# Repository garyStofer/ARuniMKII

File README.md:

# ARuniMKII
PCB  to run ERSKY firmware on old RC transmitters or DIY boxes.

-- Originated from AR9X and ARUni schematic as designed by "flygear" -- on RCgroups

See thread AR9X and ARUni on RC-Groups

Firmware discussions at openrcforums.com under erskyTx (was ersky9x)

Firmware can be found at er9x.com  maintained by Mike Blandford. Use ERSKYTX version  "9XR-PRO" 
Also Pre-Release FW at OpenRCforums : ErskyTX Test Versions by Mike Blandford.

The board is built with an AT-SAM-4 chip with twice the RAM of the original ARUni/AR9x board. See BOM file .
 
The correct chip ID has to be chosen when initially flashing the FW and bootloader to a blank chip with the SAMba tool from Atmel.

firmware src for jr9303 based implementation is at github.com/garyStofer/mbtx

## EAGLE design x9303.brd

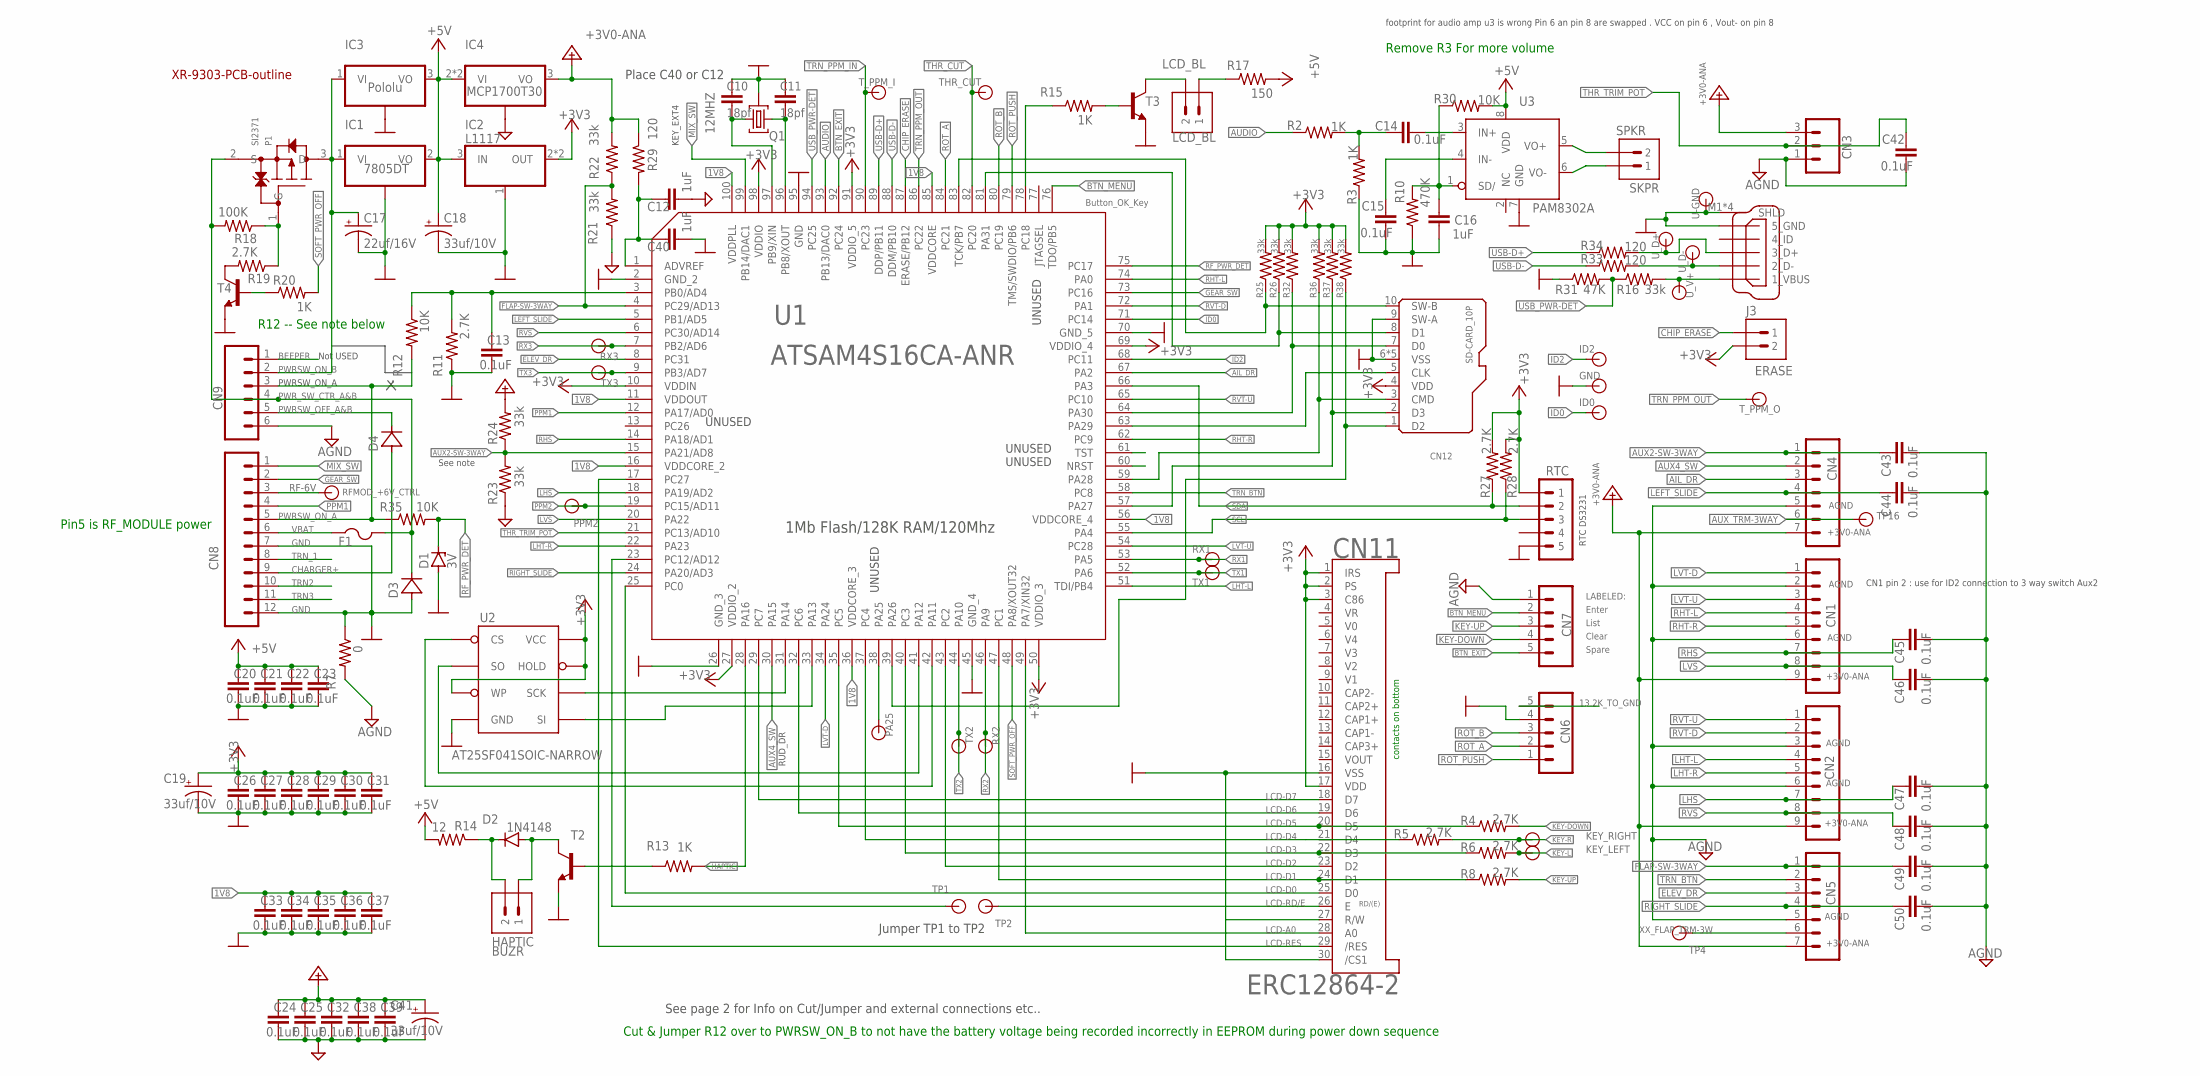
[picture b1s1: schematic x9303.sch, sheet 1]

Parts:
BUZR: HAPTIC; 1X02
C10, C11: 18pf; C0603K; DIGIKEY 1292-1494-1-ND
C12, C16, C40: 1uF; C0603K
C13, C14, C15, C20, C21, C22, C23, C24, C25, C26, C27, C28, C29, C30, C31, C32, C33, C34, C35, C36, C37, C38, C39, C42, C43, C44, C45, C46, C47, C48, C49, C50: 0.1uF; C0603K
C17: 22uf/16V; SMC_B; DIGIKEY 478-1758-1-ND
C18, C19, C41: 33uf/10V; SMC_B; DIGIKEY 478-9074-1-ND
CN1, CN2: CONN_09JST-9-PTH-V; JST-9-PTH-VERT
CN3: CONN_03JST-PTH-VERT; JST-3-PTH-VERT; DIGIKEY swr201-nrtn-s03-sa-wh
CN4: CONN_07JST-7PTH-V; JST-7-PTH-VERT
CN5: CONN_07JST-7PTH-V; JST-7-PTH-VERT; DIGIKEY 455-1709-ND
CN6: CONN_05JST-VERT; JST-5-PTH-VERT; DIGIKEY swr201-nrtn-s05-sa-wh
CN7: CONN_05JST-VERT; JST-5-PTH-VERT
CN8: CONN_12JST-12-PTH-V; JST-12-PTH-VERT; DIGIKEY 415-1714-ND
CN9: CONN_06JST-6-PTH-V; JST-6-PTH-VERT; DIGIKEY 455-1708-ND
CN11: ERC12864-2; FH12-30S-0.5SH
CN12: SD-CARD_10P; CONN8_DM3D-SF_HIR
D1: 3V; SOT23; DIGIKEY BZX84B3V0-FDICT-ND-Nd
D2: 1N4148; DO35-7
D3, D4: MURA220T3G; SMA
F1: SMD-FUSE-1206; R1206
GND: TP-1; TP
IC1: 7805DT; TO252
IC2: L1117; SOT223; DIGIKEY 497-17239-1-ND
IC3: Pololu; POLOLU
IC4: MCP1700T30; SOT89
ID0, ID2: TP-1; TP
J3: ERASE; 1X02
KEY_LEFT: TP-1; TP
KEY_RIGHT: TP-1; TP
LCD_BL: LCD_BL; 1X02
P1: SI2371; SOT23
PA25: TP-1; TP
PPM2: TP-1; TP
Q1: 12MHZ; XTAL2.4X2.7; DIGIKEY lfxtal083388RL3K
R2, R3, R13, R15, R20: 1K; R0603
R4, R5, R6, R8, R11, R19, R27, R28: 2.7K; R0603
R7: 0; R0805
R10: 470K; R0603
R12, R30, R35: 10K; R0603
R14: 12; R0805
R16, R21, R22, R23, R24, R25, R26, R32, R36, R37, R38: 33k; R0603
R17: 150; R0805
R18: 100K; R0603
R29, R33, R34: 120; R0603
R31: 47K; R0603
RF-6V: TP-1; TP
RTC: M05PTH; 1X05
RX1, RX2, RX3: TP-1; TP
SPKR: SKPR; 1X02
T2, T3, T4: MMBT3904; SOT23-BEC; DIGIKEY 2368-MMBT3904-ND
THR_CUT: TP-1; TP
TP1, TP2, TP4, TP16: TP-1; TP
TX1, TX2, TX3: TP-1; TP
T_PPM_I: TP-1; TP
T_PPM_O: TP-1; TP
U1: ATSAM4S16CA-ANR; TQFP100_14X14MC_MCH
U2: AT25SF041SOIC-NARROW; SO08
U3: PAM8302A; SOIC_2AADCR_DIO
U$1: XR9303-PCB; XR9303-PCB_OUTLINE
U-GND: TP-1; TP
U_D+: TP-1; TP
U_D-: TP-1; TP
U_V+: TP-1; TP
X2: MINI-USB-32005-201; 32005-201

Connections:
1V8: C33.2, C34.2, C35.2, C36.2, C37.2, U1.11 (VDDOUT), U1.16 (VDDCORE_2), U1.36 (VDDCORE_3), U1.56 (VDDCORE_4), U1.85 (VDDCORE), U1.100 (VDDPLL)
13.2K_TO_GND: CN6.5
+3V0-ANA: C24.2, C25.2, C32.2, C38.2, C39.2, C41.+, CN1.9, CN2.9, CN3.3, CN4.7, CN5.7, IC4.3 (VO), R22.2, R24.2, R29.1
+3V3: C19.+, C26.2, C27.2, C28.2, C29.2, C30.2, C31.2, CN11.1 (IRS), CN11.2 (PS), CN11.3 (C86), CN11.17 (VDD), CN12.4 (VDD), IC2.2 (OUT), IC2.4 (OUT), J3.2, R25.2, R26.2, R27.2, R28.2, R32.2, R36.2, R37.2, R38.2, RTC.1, U1.10 (VDDIN), U1.27 (VDDIO_2), U1.50 (VDDIO_3), U1.69 (VDDIO_4), U1.91 (VDDIO_5), U1.98 (VDDIO), U2.3 (WP), U2.7 (HOLD), U2.8 (VCC)
+5V: C18.+, C20.2, C21.2, C22.2, C23.2, IC1.2 (VO), IC2.3 (IN), IC3.3 (VO), IC4.2 (VI), IC4.4 (VI), R14.2, R17.2, R30.2, U3.8 (VDD)
AGND: C12.2, C24.1, C25.1, C32.1, C38.1, C39.1, C41.-, C42.1, C43.1, C44.1, C45.1, C46.1, C47.1, C48.1, C49.1, C50.1, CN1.2, CN1.6, CN2.3, CN2.6, CN3.1, CN4.5, CN5.5, CN7.1, CN9.6, IC4.1 (GND), R7.2, R21.1, R23.1
AIL_DR: CN4.3, U1.67 (PA2)
AUDIO: R2.1, U1.93 (PB13/DAC0)
AUX2-SW-3WAY: C43.2, CN4.1, R23.2, R24.1, U1.15 (PA21/AD8)
AUX4_SW: CN4.2, U1.30 (PA15)
AUX_TRM-3WAY: CN4.6, TP16.P$1
BEEPER: CN9.1
BTN_EXIT: CN7.5, U1.92 (PC24)
BTN_MENU: CN7.2, U1.76 (TDO/PB5)
CHARGER+: CN8.9, D4.A
CHIP_ERASE: J3.1, U1.87 (ERASE/PB12)
ELEV_DR: CN5.3, U1.8 (PC31)
FLAP-SW-3WAY: C49.2, CN5.1, R21.2, R22.1, U1.4 (PC29/AD13)
FLASH_CS: U1.42 (PA11), U2.1 (CS)
GEAR_SW: CN8.2, U1.73 (PC16)
GND: C10.1, C11.1, C13.1, C15.1, C16.2, C17.-, C18.-, C19.-, C20.1, C21.1, C22.1, C23.1, C26.1, C27.1, C28.1, C29.1, C30.1, C31.1, C33.1, C34.1, C35.1, C36.1, C37.1, C40.2, CN6.4, CN8.7, CN8.12, CN11.16 (VSS), CN11.27 (R/W), CN11.30 (/CS1), CN12.6 (VSS), CN12.9 (SW-A), CN12.GND1 (VSS), CN12.GND2 (VSS), CN12.GND3 (VSS), CN12.GND4 (VSS), D1.1 (A), D3.A, GND.P$1, IC1.3 (GND), IC2.1 (GND), IC3.2 (GND), Q1.P$2 (2), Q1.P$4 (2), R3.1, R7.1, R10.1, R11.1, R31.1, RTC.5, T2.E, T3.E, T4.E, U1.2 (GND_2), U1.26 (GND_3), U1.45 (GND_4), U1.70 (GND_5), U1.95 (GND), U2.4 (GND), U3.7 (GND), U-GND.P$1, X2.5_USB_GND (5_GND), X2.M1 (SHLD), X2.M2 (SHLD), X2.M3 (SHLD), X2.M4 (SHLD)
HAPTIC: R13.2, U1.28 (PA16)
ID0: ID0.P$1, U1.71 (PC14)
ID2: ID2.P$1, U1.68 (PC11)
KEY-DOWN: CN7.4, R4.2
KEY-L: KEY_LEFT.P$1, R6.2
KEY-R: KEY_RIGHT.P$1, R5.2
KEY-UP: CN7.3, R8.2
LCD-A0: CN11.28 (A0), U1.49 (PA7/XIN32)
LCD-D0: CN11.25 (D0), U1.25 (PC0)
LCD-D1: CN11.24 (D1), R8.1, U1.47 (PC1)
LCD-D2: CN11.23 (D2), U1.43 (PC2)
LCD-D3: CN11.22 (D3), R6.1, U1.40 (PC3)
LCD-D4: CN11.21 (D4), R5.1, U1.37 (PC4)
LCD-D5: CN11.20 (D5), R4.1, U1.35 (PC5)
LCD-D6: CN11.19 (D6), U1.32 (PC6)
LCD-D7: CN11.18 (D7), U1.29 (PC7)
LCD-RD/E: CN11.26 (E), TP2.P$1
LCD-RES: CN11.29 (/RES), U1.17 (PC27)
LCD_BL: R15.1, U1.78 (PC18)
LEFT_SLIDE: C44.2, CN4.4, U1.5 (PB1/AD5)
LHS: C47.2, CN2.7, U1.18 (PA19/AD2)
LHT-L: CN2.4, U1.51 (TDI/PB4)
LHT-R: CN2.5, U1.22 (PA23)
LVS: C46.2, CN1.8, U1.20 (PA22)
LVT-D: CN1.1, U1.34 (PA24)
LVT-U: CN1.3, U1.54 (PC28)
MIX_SW: CN8.1, U1.99 (PB14/DAC1)
unnamed: C16.1, R10.2, R30.1, U3.1 (SD/)
unnamed: R16.2, U_V+.P$1, X2.1_VBUS
unnamed: P1.1 (G), R18.1, R19.1
unnamed: R19.2, T4.C
unnamed: R34.2, U_D+.P$1, X2.3_D+
unnamed: C14.1, R2.2, R3.2
unnamed: R20.1, T4.B
unnamed: BUZR.2, D2.C, R14.1
unnamed: TP1.P$1, U1.23 (PC12/AD12)
unnamed: U1.31 (PA14), U2.6 (SCK)
unnamed: U1.33 (PA13), U2.5 (SI)
unnamed: PA25.P$1, U1.38 (PA25)
unnamed: U1.41 (PA12), U2.2 (SO)
unnamed: C10.2, Q1.P$3 (3), U1.97 (PB9/XIN)
unnamed: C11.2, Q1.P$1 (1), U1.96 (PB8/XOUT)
unnamed: CN12.8 (D1), R26.1, U1.81 (PA31)
unnamed: CN12.10 (SW-B), R25.1, U1.83 (TCK/PB7)
unnamed: CN12.7 (D0), R32.1, U1.64 (PA30)
unnamed: CN12.5 (CLK), U1.63 (PA29)
unnamed: R13.1, T2.B
unnamed: CN12.2 (D3), R37.1, U1.57 (PA27)
unnamed: CN12.1 (D2), R38.1, U1.39 (PA26)
unnamed: SPKR.2, U3.5 (VO+)
unnamed: BUZR.1, D2.A, T2.C
unnamed: R15.2, T3.B
unnamed: LCD_BL.2, T3.C
unnamed: LCD_BL.1, R17.1
unnamed: C12.1, C40.1, R29.2, U1.1 (ADVREF)
unnamed: CN12.3 (CMD), R36.1, U1.59 (PA28)
unnamed: SPKR.1, U3.6 (VO-)
unnamed: C14.2, U3.3 (IN+)
unnamed: C15.2, U3.4 (IN-)
PPM1: CN8.4, U1.12 (PA17/AD0)
PPM2: PPM2.P$1, U1.19 (PC15/AD11)
PWRSW_OFF_A&B: CN9.5, D4.C
PWRSW_ON_A: CN8.5, CN9.3, R12.2, R35.1
PWRSW_ON_B: C17.+, CN9.2, IC1.1 (VI), IC3.1 (VI), P1.3 (D)
PWR_SW_CTR_A&B: CN9.4, D3.C, F1.2, P1.2 (S), R18.2
RFMOD_+6V_CTRL: CN8.3, RF-6V.P$1
RF_PWR_DET: D1.3 (C), R35.2, U1.75 (PC17)
RHS: C45.2, CN1.7, U1.14 (PA18/AD1)
RHT-L: CN1.4, U1.74 (PA0)
RHT-R: CN1.5, U1.62 (PC9)
RIGHT_SLIDE: C50.2, CN5.4, U1.24 (PA20/AD3)
ROT_A: CN6.2, U1.84 (PC21)
ROT_B: CN6.3, U1.80 (PC19)
ROT_PUSH: CN6.1, U1.79 (TMS/SWDIO/PB6)
RVS: C48.2, CN2.8, U1.6 (PC30/AD14)
RVT-D: CN2.2, U1.72 (PA1)
RVT-U: CN2.1, U1.65 (PC10)
RX1: RX1.P$1, U1.53 (PA5)
RX2: RX2.P$1, U1.46 (PA9)
RX3: RX3.P$1, U1.7 (PB2/AD6)
SCL: R28.1, RTC.3, U1.55 (PA4)
SDA: R27.1, RTC.2, U1.66 (PA3)
SOFT_PWR_OFF: R20.2, U1.48 (PA8/XOUT32)
THR_CUT: THR_CUT.P$1, U1.82 (PC20)
THR_TRIM_POT: C42.2, CN3.2, U1.21 (PC13/AD10)
TRN2: CN8.10
TRN3: CN8.11
TRN_1: CN8.8
TRN_BTN: CN5.2, U1.58 (PC8)
TRN_PPM_IN: T_PPM_I.P$1, U1.90 (PC23)
TRN_PPM_OUT: T_PPM_O.P$1, U1.86 (PC22)
TX1: TX1.P$1, U1.52 (PA6)
TX2: TX2.P$1, U1.44 (PA10)
TX3: TX3.P$1, U1.9 (PB3/AD7)
USB-D+: R34.1, U1.89 (DDP/PB11)
USB-D-: R33.1, U1.88 (DDM/PB10)
USB_D-: R33.2, U_D-.P$1, X2.2_D-
USB_PWR-DET: R16.1, R31.2, U1.94 (PC25)
VBAT: CN8.6, F1.1
VBAT_MEAS: C13.2, R11.2, R12.1, U1.3 (PB0/AD4)
XX_FLAP_TRM-3W: CN5.6, TP4.P$1

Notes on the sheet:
LABELED:
Enter
List
Clear
Spare
Button_OK_Key
RD/(E)
RTC DS3231
1Mb Flash/128K RAM/120Mhz
RUD_DR
KEY_EXT4
UNUSED
Not USED
PWRSW_ON_A
Place C40 or C12
Jumper TP1 to TP2
See note
footprint for audio amp u3 is wrong Pin 6 an pin 8 are swapped . VCC on pin 6 , Vout- on pin 8
CN1 pin 2 : use for ID2 connection to 3 way switch Aux2
See page 2 for Info on Cut/Jumper and external connections etc..
contacts on bottom
Cut & Jumper R12 over to PWRSW_ON_B to not have the battery voltage being recorded incorrectly in EEPROM during power down sequence
R12 -- See note below
Pin5 is RF_MODULE power
Remove R3 For more volume

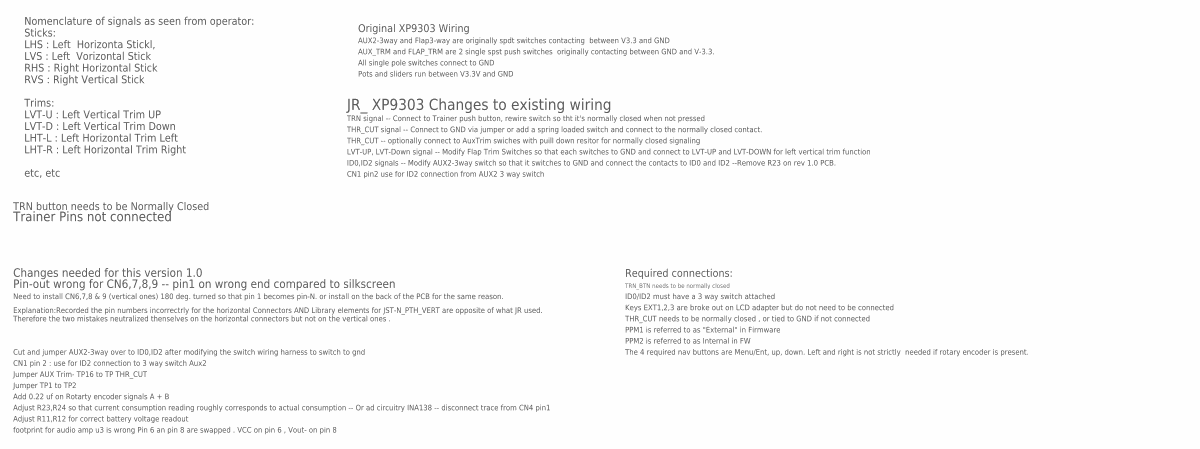
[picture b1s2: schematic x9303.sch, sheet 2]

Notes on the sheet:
Nomenclature of signals as seen from operator: Sticks: LHS : Left Horizonta Stickl, LVS : Left Vorizontal Stick RHS : Right Horizontal Stick RVS : Right Vertical Stick Trims: LVT-U : Left Vertical Trim UP LVT-D : Left Vertical Trim Down LHT-L : Left Horizontal Trim Left LHT-R : Left Horizontal Trim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
AUX_TRM and FLAP_TRM are 2 single spst push switches originally contacting between GND and V-3.3.
JR_ XP9303 Changes to existing wiring
All single pole switches connect to GND
Pots and sliders run between V3.3V and GND
THR_CUT signal -- Connect to GND via jumper or add a spring loaded switch and connect to the normally closed contact.
Trainer Pins not connected
TRN button needs to be Normally Closed
AUX2-3way and Flap3-way are originally spdt switches contacting between V3.3 and GND
TRN signal -- Connect to Trainer push button, rewire switch so tht it's normally closed when not pressed
LVT-UP, LVT-Down signal -- Modify Flap Trim Switches so that each switches to GND and connect to LVT-UP and LVT-DOWN for left vertical trim function
ID0,ID2 signals -- Modify AUX2-3way switch so that it switches to GND and connect the contacts to ID0 and ID2 --Remove R23 on rev 1.0 PCB.
THR_CUT -- optionally connect to AuxTrim swiches with puill down resitor for normally closed signaling
CN1 pin2 use for ID2 connection from AUX2 3 way switch
Original XP9303 Wiring
Changes needed for this version 1.0
Pin-out wrong for CN6,7,8,9 -- pin1 on wrong end compared to silkscreen
Cut and jumper AUX2-3way over to ID0,ID2 after modifying the switch wiring harness to switch to gnd
Jumper AUX Trim- TP16 to TP THR_CUT
footprint for audio amp u3 is wrong Pin 6 an pin 8 are swapped . VCC on pin 6 , Vout- on pin 8
CN1 pin 2 : use for ID2 connection to 3 way switch Aux2
Add 0.22 uf on Rotarty encoder signals A + B
Jumper TP1 to TP2
Adjust R11,R12 for correct battery voltage readout
Adjust R23,R24 so that current consumption reading roughly corresponds to actual consumption -- Or ad circuitry INA138 -- disconnect trace from CN4 pin1
Need to install CN6,7,8 & 9 (vertical ones) 180 deg. turned so that pin 1 becomes pin-N. or install on the back of the PCB for the same reason.
Explanation:Recorded the pin numbers incorrectrly for the horizontal Connectors AND Library elements for JST-N_PTH_VERT are opposite of what JR used. Therefore the two mistakes neutralized thenselves on the horizontal connectors but not on the vertical ones .
TRN_BTN needs to be normally closed
Keys EXT1,2,3 are broke out on LCD adapter but do not need to be connected
ID0/ID2 must have a 3 way switch attached
Required connections:
THR_CUT needs to be normally closed , or tied to GND if not connected
PPM1 is referred to as "External" in Firmware
PPM2 is referred to as Internal in FW
The 4 required nav buttons are Menu/Ent, up, down. Left and right is not strictly needed if rotary encoder is present.

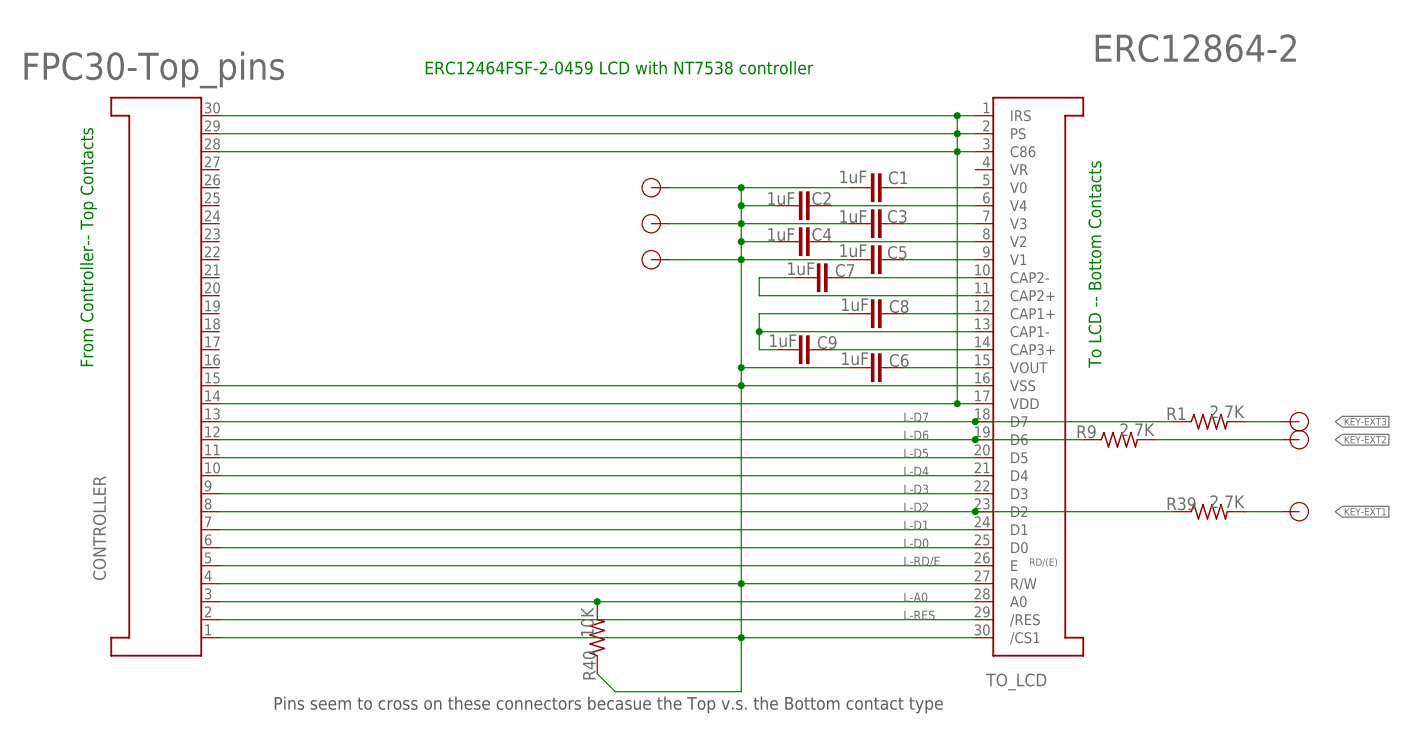
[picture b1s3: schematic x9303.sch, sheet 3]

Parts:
C1, C2, C3, C4, C5, C6, C7, C8, C9: 1uF; C0805
CONTROLLER: FPC30-Top_pins; FH12-30S-0.5SH; DIGIKEY 732-3517-ND
K1, K2, K3: TP-1; TP
K_EXT4, K_EXT5, K_EXT6: TP-1; TP
R1, R9, R39: 2.7K; R0603
R40: 10K; R0603
TO_LCD: ERC12864-2; FH12-30S-0.5SH; DIGIKEY 732-3518-ND

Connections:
KEY-EXT1: K1.P$1, R39.2
KEY-EXT2: K2.P$1, R9.2
KEY-EXT3: K3.P$1, R1.2
L-A0: CONTROLLER.3, R40.2, TO_LCD.28 (A0)
L-D0: CONTROLLER.6, TO_LCD.25 (D0)
L-D1: CONTROLLER.7, TO_LCD.24 (D1)
L-D2: CONTROLLER.8, R39.1, TO_LCD.23 (D2)
L-D3: CONTROLLER.9, TO_LCD.22 (D3)
L-D4: CONTROLLER.10, TO_LCD.21 (D4)
L-D5: CONTROLLER.11, TO_LCD.20 (D5)
L-D6: CONTROLLER.12, R9.1, TO_LCD.19 (D6)
L-D7: CONTROLLER.13, R1.1, TO_LCD.18 (D7)
L-RD/E: CONTROLLER.5, TO_LCD.26 (E)
L-RES: CONTROLLER.2, TO_LCD.29 (/RES)
L_GND: C1.2, C2.2, C3.2, C4.2, C5.2, C6.2, CONTROLLER.1, CONTROLLER.4, CONTROLLER.15, K_EXT4.P$1, K_EXT5.P$1, K_EXT6.P$1, R40.1, TO_LCD.16 (VSS), TO_LCD.27 (R/W), TO_LCD.30 (/CS1)
L_VDD: CONTROLLER.14, CONTROLLER.28, CONTROLLER.29, CONTROLLER.30, TO_LCD.1 (IRS), TO_LCD.2 (PS), TO_LCD.3 (C86), TO_LCD.17 (VDD)
unnamed: C1.1, TO_LCD.5 (V0)
unnamed: C2.1, TO_LCD.6 (V4)
unnamed: C3.1, TO_LCD.7 (V3)
unnamed: C4.1, TO_LCD.8 (V2)
unnamed: C5.1, TO_LCD.9 (V1)
unnamed: C7.1, TO_LCD.10 (CAP2-)
unnamed: C7.2, TO_LCD.11 (CAP2+)
unnamed: C8.2, C9.2, TO_LCD.13 (CAP1-)
unnamed: C8.1, TO_LCD.12 (CAP1+)
unnamed: C9.1, TO_LCD.14 (CAP3+)
unnamed: C6.1, TO_LCD.15 (VOUT)

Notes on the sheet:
RD/(E)
From Controller-- Top Contacts
To LCD -- Bottom Contacts
Pins seem to cross on these connectors becasue the Top v.s. the Bottom contact type
ERC12464FSF-2-0459 LCD with NT7538 controller

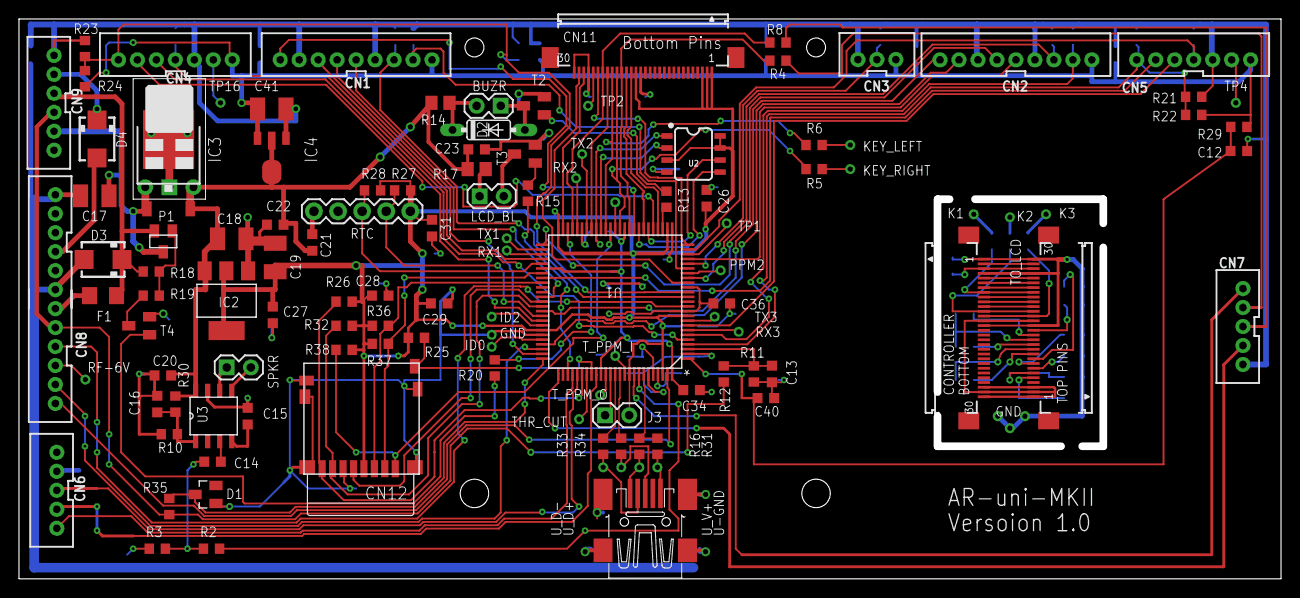
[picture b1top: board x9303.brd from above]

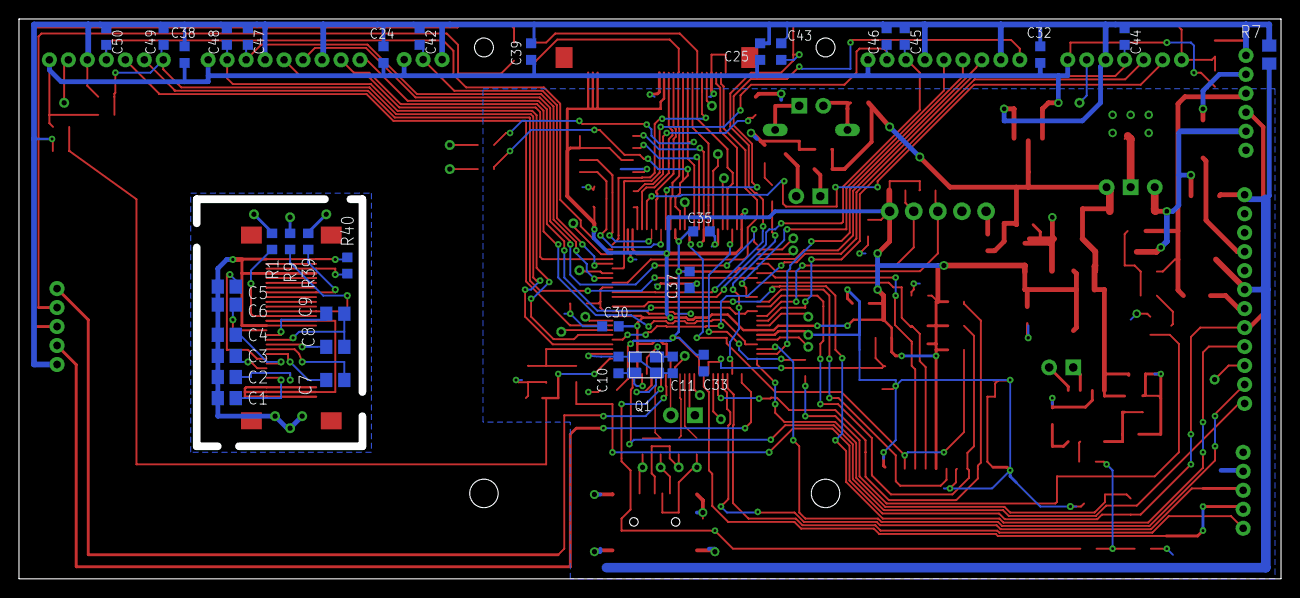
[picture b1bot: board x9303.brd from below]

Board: 2 copper layers, 132.2 x 58.2 mm, 158 parts (35 on the bottom side), 144 nets.

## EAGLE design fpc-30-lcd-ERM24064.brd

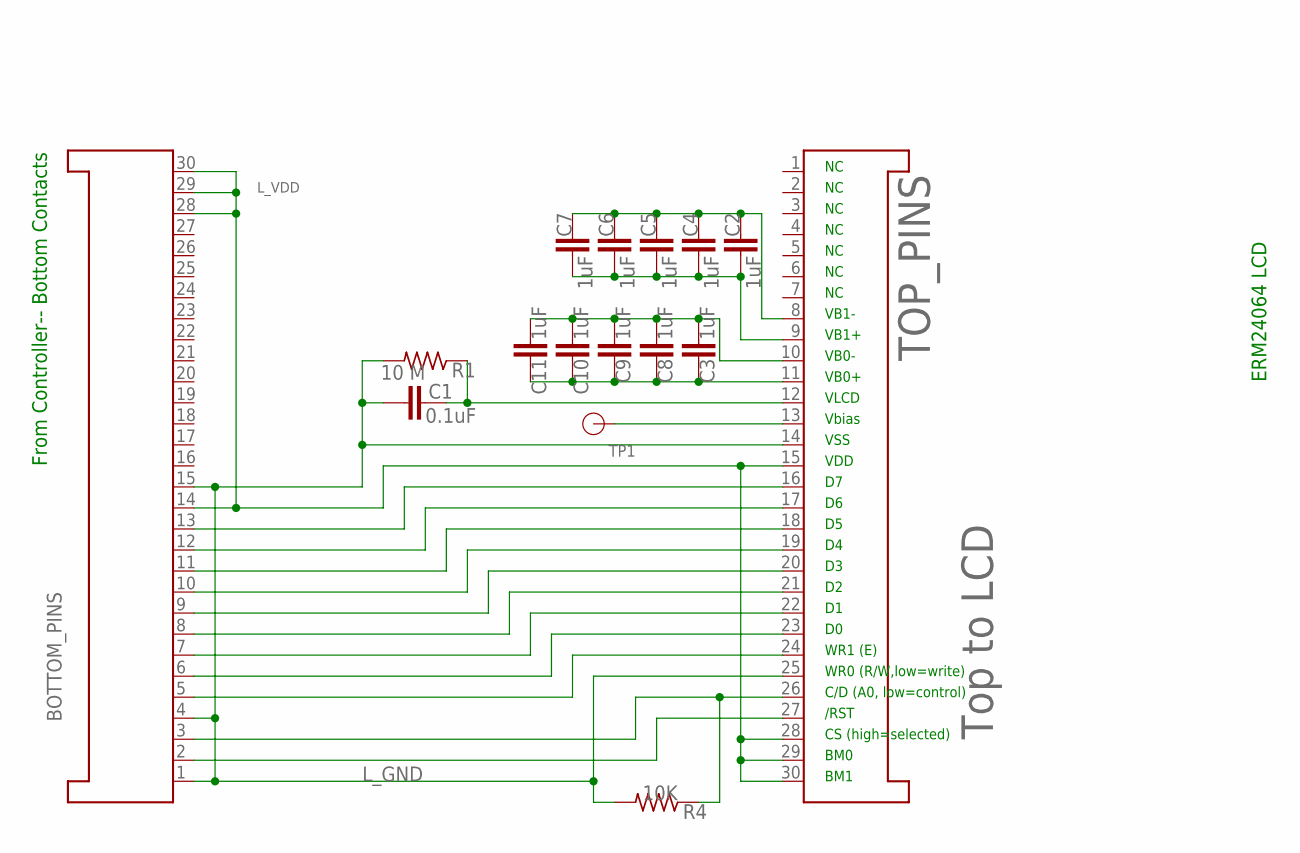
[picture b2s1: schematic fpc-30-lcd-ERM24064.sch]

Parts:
BOTTOM_PINS: FPC30-bottom_pins; FH12-30S-0.5SH; DIGIKEY 732-3517-ND
C1: 0.1uF; C0603K
C2, C3, C4, C5, C6, C7, C8, C9, C10, C11: 1uF; C0603K
R1: 10 M; R0603
R4: 10K; R0603
TOP_PINS: Top to LCD; FH12-30S-0.5SH
TP1: TP-1; TP

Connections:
L-A0: BOTTOM_PINS.3, R4.1, TOP_PINS.26
L-D0: BOTTOM_PINS.6, TOP_PINS.23
L-D1: BOTTOM_PINS.7, TOP_PINS.22
L-D3: BOTTOM_PINS.9, TOP_PINS.20
L-D4: BOTTOM_PINS.10, TOP_PINS.19
L-D5: BOTTOM_PINS.11, TOP_PINS.18
L-D6: BOTTOM_PINS.12, TOP_PINS.17
L-RD/E: BOTTOM_PINS.5, TOP_PINS.24
L-RES: BOTTOM_PINS.2, TOP_PINS.27
L_D7: BOTTOM_PINS.13, TOP_PINS.16
L_GND: BOTTOM_PINS.1, BOTTOM_PINS.4, BOTTOM_PINS.15, C1.2, R1.2, R4.2, TOP_PINS.14, TOP_PINS.25
L_VDD: BOTTOM_PINS.14, BOTTOM_PINS.28, BOTTOM_PINS.29, BOTTOM_PINS.30, TOP_PINS.15, TOP_PINS.28, TOP_PINS.29, TOP_PINS.30
unnamed: C1.1, R1.1, TOP_PINS.12
unnamed: TOP_PINS.13, TP1.P$1
unnamed: C2.1, C4.1, C5.1, C6.1, C7.1, TOP_PINS.8
unnamed: C3.2, C8.2, C9.2, C10.2, C11.2, TOP_PINS.10
unnamed: C2.2, C4.2, C5.2, C6.2, C7.2, TOP_PINS.9
unnamed: C3.1, C8.1, C9.1, C10.1, C11.1, TOP_PINS.11
unnamed: BOTTOM_PINS.8, TOP_PINS.21

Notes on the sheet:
From Controller-- Bottom Contacts
ERM24064 LCD
VB1-
VB1+
VB0-
VB0+
VLCD
Vbias
VSS
VDD
WR1 (E)
WR0 (R/W,low=write)
C/D (A0, low=control)
/RST
CS (high=selected)
BM0
BM1

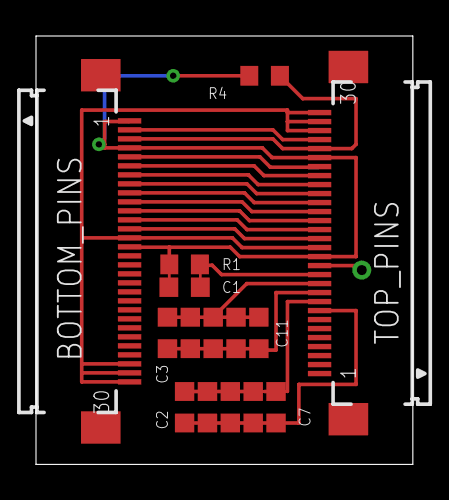
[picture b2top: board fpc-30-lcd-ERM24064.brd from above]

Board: 2 copper layers, 20.9 x 23.8 mm, 16 parts (0 on the bottom side), 19 nets.

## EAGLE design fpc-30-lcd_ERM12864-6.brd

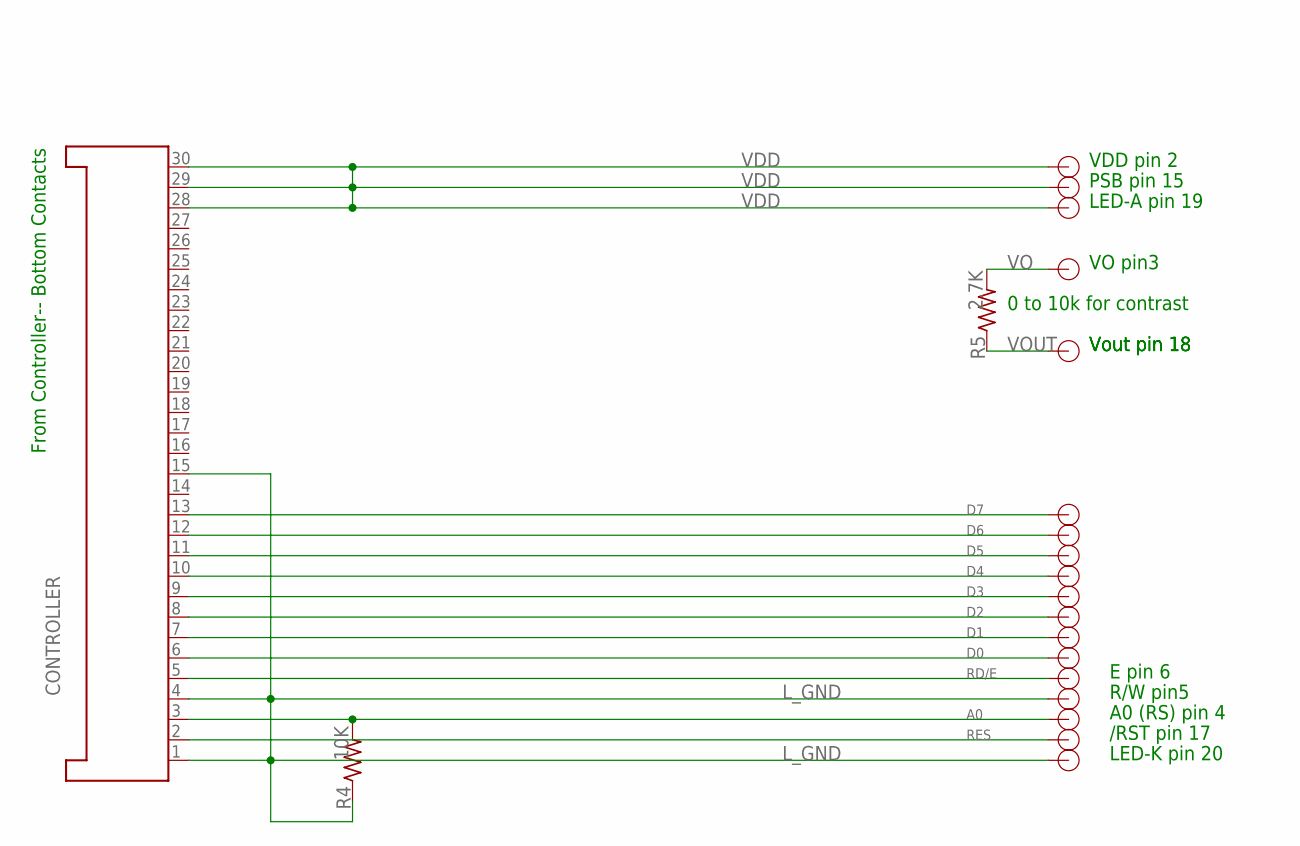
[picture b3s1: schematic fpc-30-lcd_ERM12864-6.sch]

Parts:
/RST: TP-1; TP
A0/RS: TP-1; TP
CONTROLLER: FPC30-Top_pins; FH12-30S-0.5SH; DIGIKEY 732-3517-ND
D0, D7: D7; TP
D1, D2, D3, D4, D5, D6: TP-1; TP
LED_A: TP-1; TP
LED_K: TP-1; TP
PSB: TP-1; TP
R4: 10K; R0603
R5: 2.7K; R0603
R/W: TP-1; TP
RD/E: TP-1; TP
VDD: TP-1; TP
VO: D7; TP
VOUT: D7; TP

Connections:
A0: A0/RS.P$1, CONTROLLER.3, R4.2
D0: CONTROLLER.6, D0.P$1
D1: CONTROLLER.7, D1.P$1
D2: CONTROLLER.8, D2.P$1
D3: CONTROLLER.9, D3.P$1
D4: CONTROLLER.10, D4.P$1
D5: CONTROLLER.11, D5.P$1
D6: CONTROLLER.12, D6.P$1
D7: CONTROLLER.13, D7.P$1
L_GND: CONTROLLER.1, CONTROLLER.4, CONTROLLER.15, LED_K.P$1, R4.1, R/W.P$1
RD/E: CONTROLLER.5, RD/E.P$1
RES: /RST.P$1, CONTROLLER.2
VDD: CONTROLLER.28, CONTROLLER.29, CONTROLLER.30, LED_A.P$1, PSB.P$1, VDD.P$1
VO: R5.2, VO.P$1
VOUT: R5.1, VOUT.P$1

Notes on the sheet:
From Controller-- Bottom Contacts
VDD pin 2
PSB pin 15
A0 (RS) pin 4
R/W pin5
/RST pin 17
E pin 6
LED-K pin 20
LED-A pin 19
VO pin3
Vout pin 18
0 to 10k for contrast

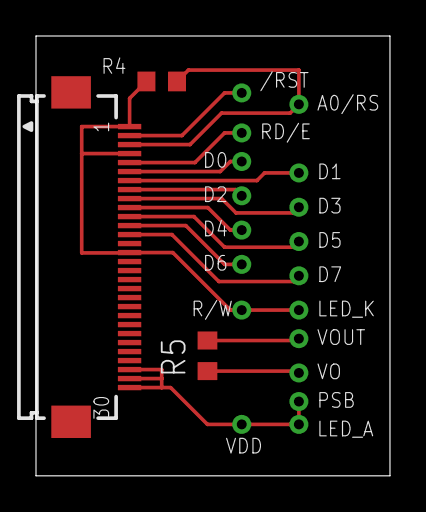
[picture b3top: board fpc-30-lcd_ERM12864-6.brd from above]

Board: 2 copper layers, 19.7 x 24.4 mm, 21 parts (0 on the bottom side), 15 nets.

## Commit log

2021-04-22 Initial check in
2021-04-22 Added prior docs and current tools
2021-04-22 added labels for connector pins on layout layer 150
2022-02-24 no change just added empty text file
2024-04-06 added pictures and docs added firmware binary added old JR9303 wiring and pin-out doc added lcd display adapter patch boards for different displays
2024-06-05 added binaries supporting new LCD modules added pdf on how to bootstrap with SAMBA added schematic and layout pictures in PNG format
